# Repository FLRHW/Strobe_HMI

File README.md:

<h1 align="center">HMI board</h1>

<p align="center" width="100%">
  
</p>

***

<p align="center">
  
&nbsp; &nbsp; &nbsp; &nbsp;
  
</p>

***

# **1 kV strobe - Intro**
Since my tenage years I spend a great chunk of my spare time on hobby electronics. Back then, much of that time was to build FM transmitters, audio amplifiers and strobe lights. I was always pushing my builds as much as I could, (i.e., extracting pressurised smoke from capacitors!) as an attempt to make the flashes ever brighter. It was somewhat challenging given the limited experience and resources I had at the time, but a lot of fun nonetheless.
Life went on, priorities changed and for a long time I did not "play" with strobe lights... until recently, after I bumped into an ebay page of a large XOP-15 bulb and, well, nostalgy happened.

While defining the project scope, I had to decide if I'd use the good old Xenon bulb or move to LEDs, as these have greatly evolved and are ubiquitous nowadays, making their way to commercial strobes (https://www.martin.com/en/products/atomic-3000-led). I have decided to stick to vintage tech, as in my mind this would perhaps bring more interesting power electronics challenges, since the bulb requires a somewhat high bus voltage and can draw very high peak currents when ionised.

So that's what this repo contains: a Xenon-based strobe light, aiming to drive a XOP-15 bulb with up to 1 kV, while controlling the duration and frequency of pulses.

## Project overview
This repository contains KiCad v9 design files for the HMI board of a Xenon-based strobe light system.
The system is divided into three separate boards:
- HMI - so the user can set desired operating conditions (bus voltage, pulse width and pulse frequency)
- Main board - drives the Xenon bulb, generating the trigger pulse and actively interrupting the discharge according to the required pulse width
- Power supply - to produce an adjustable DC supply. To realise that I intend to eventually design an AC-mains powered converter, including a PFC circuit. As an interim solution, off-the-shelf boost converter modules are used: two such modules are connected in series, each providing up to 450 V output while supplied by 12 V batteries.

Working prototypes exist for both the HMI and main board. This repository covers only the HMI board. The main board is available on its own repo:
https://github.com/FLRHW/Strobe_main

The source code is kept on a separate repo:
https://github.com/FLRHW/Strobe_HMI_source

As a side project, the boost modules have been reverse engineered with the aim to modify them from non-isolated to isolated. This work is covered under the following repos:
- https://github.com/FLRHW/StepUp_module_12to450V
- https://github.com/FLRHW/Isolated_12to450V.

## Design targets
DC bus voltage: 400 V to 1000 V  
Flash rate: 0.1 Hz to 100 Hz  
Pulse duration: 20 μs to 10 ms  

Please note that extremes are not simultaneously achievable. This design relies on storing energy on a capacitor bank to then discharge it into the bulb, hence some time must be reserved for storing that energy. The pulse duration is currently limited in SW to 50 % of the period as a safeguard, but for practical use it must be a much lower percentage.

Also, the output capacitors currently in use are not large enough to reach 10 ms pulse duration - at least not at high output voltages as the bulb current seems to increase non linearly with the bus voltage.

## Intended use
This repository is intended for:
* Educational use and study of the circuit;
* Integration into hobby or research projects.

## License
The design files and documentation in this repository are released under the CERN Open Hardware Licence v2 – Permissive (CERN‑OHL‑P‑2.0). SPDX identifier: CERN-OHL-P-2.0 See the LICENSE file for the full legal text and conditions.
In short and non‑legal terms, you are free to use, modify, manufacture, and distribute hardware based on these files, provided you respect attribution requirements and the terms in the license.

## Trademarks and third‑party rights
All product names, logos, and brands eventually mentioned are the property of their respective owners and are not included or licensed here.
Any reference to third‑party marks is purely descriptive and does not imply endorsement or affiliation.

## Safety and disclaimer
* The author takes no responsibility for any injury, death or damage arising from the use, direct or indirect, of the design or otherwise any information from this repository
* You shall not build this or any prototype based on this design unless you are absolutely sure of your abilities dealing with this type of circuit
* High voltage can cause injury, death, or damage to equipment. Ensure appropriate protections and testing procedures are followed
* The design is provided as is, with no warranty of any kind
* Users are responsible for checking any patent, copyright, or regulatory constraints that may apply to their own use

***

## DIRECTORY STRUCTURE
    │
    ├─ Computations       # Misc calculations
    ├─ HTML               # HTML files for generated webpage
    ├─ Images             # Pictures and renders
    │
    ├─ kibot_resources    # External resources for KiBot
    │  ├─ colors          # Color theme for KiCad
    │  ├─ fonts           # Fonts used in the project
    │  ├─ scripts         # External scripts used with KiBot
    │  └─ templates       # Templates for KiBot generated reports
    │
    ├─ kibot_yaml         # KiBot YAML config files
    ├─ KiRI               # KiRI (PCB diff viewer) files
    │
    ├─ lib                # KiCad footprint and symbol libraries
    │  ├─ 3d_models       # Component 3D models
    │  ├─ lib_fp          # Footprint libraries
    │  └─ lib_sym         # Symbol libraries
    │
    ├─ Logos              # Logos
    │
    ├─ Manufacturing      # Assembly and fabrication documents
    │  ├─ Assembly        # Assembly documents (BoM, pos, notes)
    │  │
    │  └─ Fabrication     # Fabrication documents (ZIP, notes)
    │     ├─ Drill Tables # CSV drill tables
    │     └─ Gerbers      # Gerbers
    │
    ├─ Report             # Reports for ERC/DRC
    ├─ Schematic          # PDF of schematic
    ├─ Templates          # Title block templates
    ├─ Testing
    │  └─ Testpoints      # Testpoints tables      
    │
    └─ Variants           # Outputs for assembly variants

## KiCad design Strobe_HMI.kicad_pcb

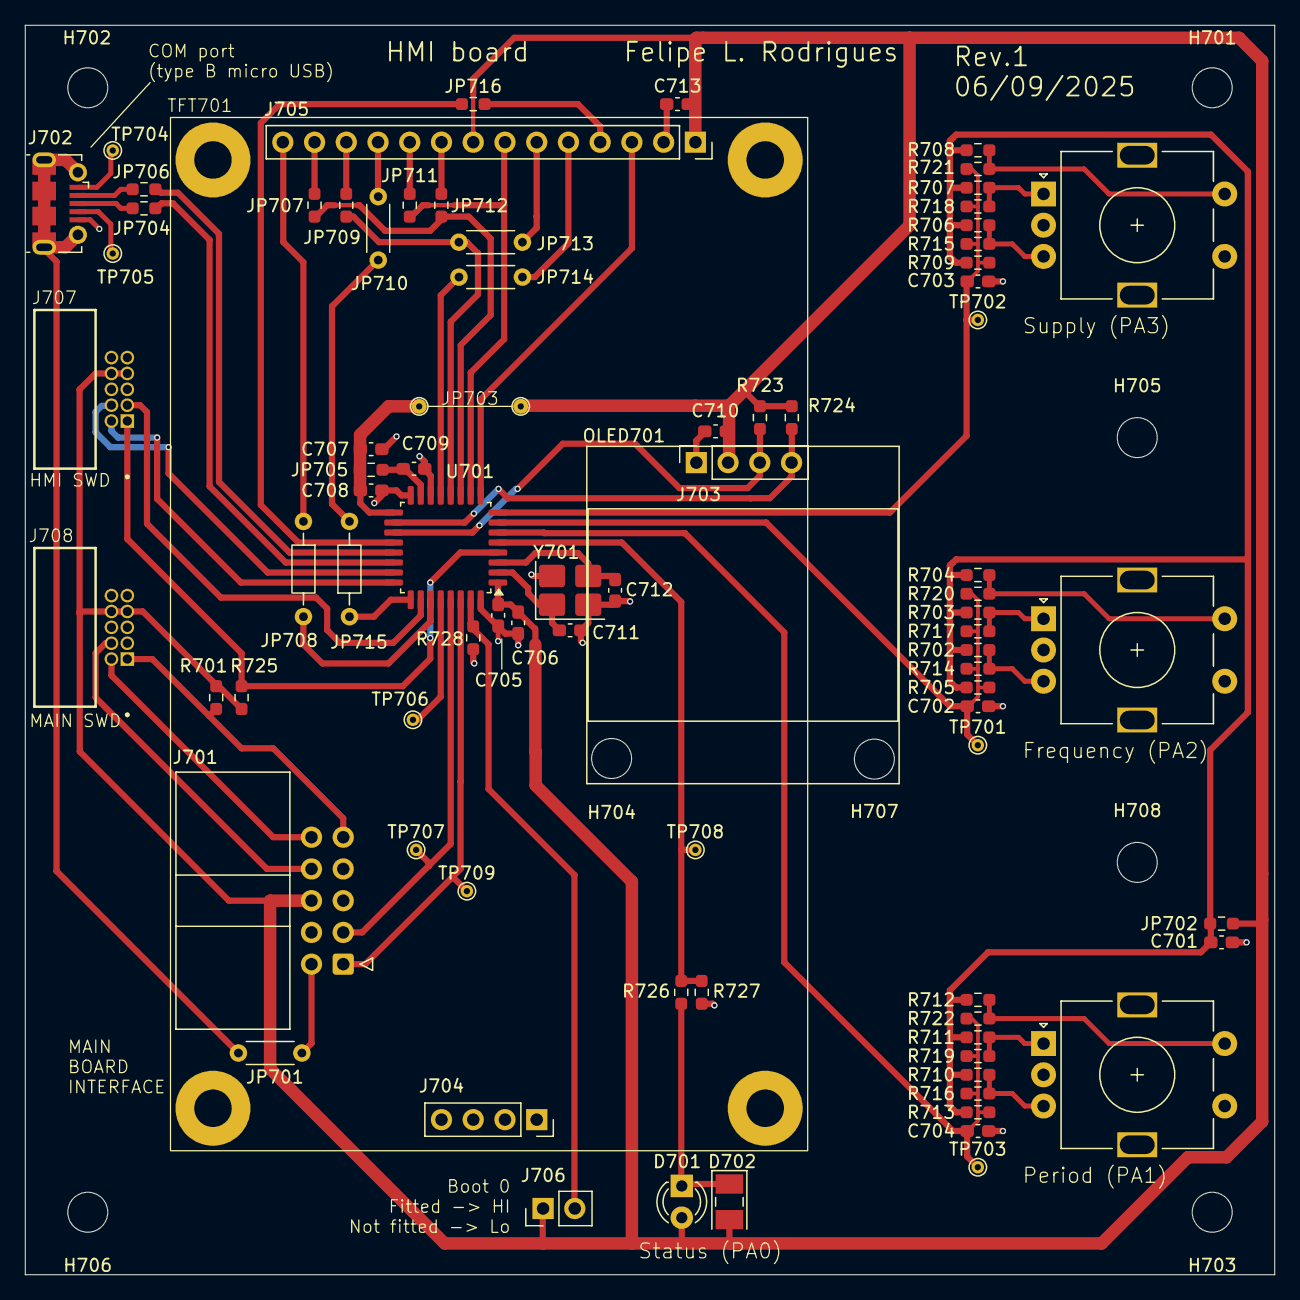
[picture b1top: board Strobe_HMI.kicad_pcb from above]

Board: 2 copper layers, 100.0 x 100.0 mm, 91 parts (0 on the bottom side), 60 nets.

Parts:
C701, C702, C703, C704, C705, C708, C709, C710, C713: 100n; C_0603_1608Metric_Pad1.08x0.95mm_HandSolder
C706, C707: 1u; C_0603_1608Metric_Pad1.08x0.95mm_HandSolder
C711, C712: 22p; C_0603_1608Metric_Pad1.08x0.95mm_HandSolder
D701: LED; LED_D3.0mm
D702: LED; LED_PLCC-2_3x2mm_KA
H701, H702, H703, H704, H705, H706, H707, H708: MountingHole; MountingHole_3.2mm_M3
J701: ZHOURI DC3; IDC-Header_2x05_P2.54mm_Horizontal
J702: 1050171001 Micro Type B; USB_Micro-B_Molex-105017-0001
J703, J704: Conn_01x04_Pin; PinSocket_1x04_P2.54mm_Vertical
J705: Conn_01x14_Pin; PinSocket_1x14_P2.54mm_Vertical
J706: Header; PinHeader_1x02_P2.54mm_Vertical
J707, J708: HX JN1.27-2x5 WZ H4.9; JN1.27-2x5 WZ H4.9
JP701, JP710, JP713, JP714: 0R; R_Axial_DIN0204_L3.6mm_D1.6mm_P5.08mm_Horizontal
JP702, JP704, JP705, JP706, JP707, JP709, JP711, JP712, JP716: 0R; R_0603_1608Metric_Pad0.98x0.95mm_HandSolder
JP703: 8.12; Jumper_mm_L8.12_D1.2_H0.5
JP708, JP715: 0R; R_Axial_DIN0204_L3.6mm_D1.6mm_P7.62mm_Horizontal
OLED701: OLED_128x64_SSD1306; OLED_SSD1306_no_pins
R701, R725, R727, R728: 10k; R_0603_1608Metric_Pad0.98x0.95mm_HandSolder
R702, R703, R704, R706, R707, R708, R710, R711, R712, R726: 1k; R_0603_1608Metric_Pad0.98x0.95mm_HandSolder
R705, R709, R713: 220k; R_0603_1608Metric_Pad0.98x0.95mm_HandSolder
R714, R715, R716: 44k; R_0603_1608Metric_Pad0.98x0.95mm_HandSolder
R717, R718, R719: 22k; R_0603_1608Metric_Pad0.98x0.95mm_HandSolder
R720, R721, R722: 11k; R_0603_1608Metric_Pad0.98x0.95mm_HandSolder
R723, R724: 4k7; R_0603_1608Metric_Pad0.98x0.95mm_HandSolder
SW701, SW702, SW703: EncSw; RotaryEncoderSwitch_Oblong
TFT701: TFT_2.8in_320x240; TFT_2.8_IN_320x240
TP701, TP702, TP703, TP704, TP705, TP706, TP707, TP708, TP709: TestPoint; TestPoint_THTPad_D1.0mm_Drill0.5mm
U701: STM32G431K8Tx; LQFP-32_7x7mm_P0.8mm
Y701: 20 MHz; Crystal_SMD_3225-4Pin_3.2x2.5mm_HandSoldering

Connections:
/Block diagram/HMI/BOOT0: J706.2, R728.1, U701.31 (PB8)
/Block diagram/HMI/DISP_CS: J705.3, U701.9 (PA4)
/Block diagram/HMI/DISP_DC: JP714.1, U701.13 (PB0)
/Block diagram/HMI/DISP_MISO: JP707.1, JP712.1, U701.11 (PA6)
/Block diagram/HMI/DISP_MOSI: JP709.1, JP713.1, U701.12 (PA7)
/Block diagram/HMI/DISP_RST: JP716.1, U701.20 (PA10)
/Block diagram/HMI/DISP_SCK: J705.7, JP711.1, U701.10 (PA5)
/Block diagram/HMI/DISP_SCL: J703.3, R723.2, U701.19 (PA9)
/Block diagram/HMI/DISP_SDA: J703.4, R724.2, U701.18 (PA8)
/Block diagram/HMI/FREQ: C702.1, R705.2, R714.2, R717.2, R720.2, TP701.1, U701.7 (PA2)
/Block diagram/HMI/LV_NRST: J701.9, J708.1, R701.2
/Block diagram/HMI/LV_RX: J701.1, TP709.1, U701.30 (PB7)
/Block diagram/HMI/LV_SWDCLK: J701.10, J708.2
/Block diagram/HMI/LV_SWDIO: J701.8, J708.4
/Block diagram/HMI/LV_TX: J701.3, TP707.1, U701.29 (PB6)
/Block diagram/HMI/NRST: J707.1, R725.2, U701.4 (PG10)
/Block diagram/HMI/PER: C704.1, R713.2, R716.2, R719.2, R722.2, TP703.1, U701.6 (PA1)
/Block diagram/HMI/SL3: C705.1, C706.1, C710.1, C713.1, D701.2 (A), D702.2 (A), J701.6, J703.2, J705.1, J705.8, J706.1, J707.7, J707.8, J708.7, J708.8, JP702.2 (B), JP703.2 (B), R701.1, R723.1, R724.1, R725.1, U701.1 (VDD)
/Block diagram/HMI/SL3_A: C709.1, JP705.2 (B), U701.15 (VDDA)
/Block diagram/HMI/SL3_J: C707.1, C708.1, JP703.1 (A), JP705.1 (A), U701.17 (VDD)
/Block diagram/HMI/ST_LED: R726.2, R727.1, TP708.1, U701.5 (PA0)
/Block diagram/HMI/SUP: C703.1, R709.2, R715.2, R718.2, R721.2, TP702.1, U701.8 (PA3)
/Block diagram/HMI/SWDCLK: J707.2, U701.24 (PA14)
/Block diagram/HMI/SWDIO: J707.4, U701.23 (PA13)
/Block diagram/HMI/SWO: J707.3, U701.26 (PB3)
/Block diagram/HMI/TCH_CS: JP710.1, JP715.2 (B)
/Block diagram/HMI/TCH_IRQ: J705.14, JP708.1 (A)
/Block diagram/HMI/USB_DM: JP706.2, U701.21 (PA11)
/Block diagram/HMI/USB_DP: JP704.2, U701.22 (PA12)
Earth: J702.6 (Shield), JP701.2
GND: C701.2, C702.2, C703.2, C704.2, C705.2, C706.2, C707.2, C708.2, C709.2, C710.2, C711.2, C712.2, C713.2, J701.5, J702.5 (GND), J703.1, J705.2, J707.5, J707.6, J708.5, J708.6, R727.2, R728.2, SW701.C, SW701.S2, SW702.C, SW702.S2, SW703.C, SW703.S2, U701.14 (VSSA), U701.16 (VSS), U701.32 (VSS), Y701.2 (G), Y701.4 (G)
unnamed: D701.1 (K), D702.1 (K), R726.1
unnamed: J701.2, JP701.1
unnamed: J702.3 (D+), JP704.1
unnamed: J702.2 (D-), JP706.1
unnamed: J702.4 (ID), TP705.1
unnamed: J702.1 (VBUS), TP704.1
unnamed: J705.4, JP716.2
unnamed: J705.5, JP714.2
unnamed: J705.6, JP713.2
unnamed: J705.9, JP712.2
unnamed: J705.10, JP711.2
unnamed: J705.11, JP710.2
unnamed: J705.12, JP709.2
unnamed: J705.13, JP707.2
unnamed: C701.1, JP702.1 (A), R702.1, R703.1, R704.1, R705.1, R706.1, R707.1, R708.1, R709.1, R710.1, R711.1, R712.1, R713.1
unnamed: JP708.2 (B), U701.27 (PB4)
unnamed: JP715.1 (A), U701.25 (PA15)
unnamed: R702.2, R714.1, SW701.B
unnamed: R703.2, R717.1, SW701.A
unnamed: R704.2, R720.1, SW701.S1
unnamed: R706.2, R715.1, SW702.B
unnamed: R707.2, R718.1, SW702.A
unnamed: R708.2, R721.1, SW702.S1
unnamed: R710.2, R716.1, SW703.B
unnamed: R711.2, R719.1, SW703.A
unnamed: R712.2, R722.1, SW703.S1
unnamed: TP706.1, U701.28 (PB5)
unnamed: C711.1, U701.2 (PF0), Y701.1
unnamed: C712.1, U701.3 (PF1), Y701.3

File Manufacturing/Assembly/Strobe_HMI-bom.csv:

Row,Quantity Per PCB,References,Value,Datasheet,Footprint,Description,Manufacturer,Manufacturer Part Number,Supplier Part Number
1,2,C711 C712,22p,~,C_0603_1608Metric_Pad1.08x0.95mm_HandSolder,Unpolarized capacitor,,,
2,8,C701 C702 C703 C704 C705 C708 C709 C713,100n,~,C_0603_1608Metric_Pad1.08x0.95mm_HandSolder,Unpolarized capacitor,,,
3,2,C706 C707,1u,~,C_0603_1608Metric_Pad1.08x0.95mm_HandSolder,Unpolarized capacitor,,,
4,1,D702,LED,~,LED_PLCC-2_3x2mm_KA,Light emitting diode,Osram,LH T6MF-GGHH-1-E3L3,
5,7,J701 J702 J704 J705 J706 J707 J708,ZHOURI DC3,~,IDC-Header_2x05_P2.54mm_Horizontal,"Generic connector, double row, 02x05, odd/even pin numbering scheme (row 1 odd numbers, row 2 even numbers), script generated (kicad-library-utils/schlib/autogen/connector/) USB Micro Type B connector Generic connector, single row, 01x04, script generated Generic connector, single row, 01x14, script generated Generic connector, single row, 01x02, script generated",,,
6,6,JP701 JP708 JP710 JP713 JP714 JP715,0R,~,R_Axial_DIN0204_L3.6mm_D1.6mm_P5.08mm_Horizontal,Jumper,Generic,Hand cut wire,
7,9,JP702 JP704 JP705 JP706 JP707 JP709 JP711 JP712 JP716,0R,~,R_0603_1608Metric_Pad0.98x0.95mm_HandSolder,Jumper,Yageo,RC0603JR-130RP,
8,1,JP703,8.12,~,Jumper_mm_L8.12_D1.2_H0.5,"Jumper, 2-pole, closed/bridged",Generic,Hand cut wire,
9,10,R702 R703 R704 R706 R707 R708 R710 R711 R712 R726,1k,~,R_0603_1608Metric_Pad0.98x0.95mm_HandSolder,Resistor,,,
10,2,R723 R724,4k7,~,R_0603_1608Metric_Pad0.98x0.95mm_HandSolder,Resistor,,,
11,4,R701 R725 R727 R728,10k,~,R_0603_1608Metric_Pad0.98x0.95mm_HandSolder,Resistor,,,
12,3,R720 R721 R722,11k,~,R_0603_1608Metric_Pad0.98x0.95mm_HandSolder,Resistor,,,
13,3,R717 R718 R719,22k,~,R_0603_1608Metric_Pad0.98x0.95mm_HandSolder,Resistor,,,
14,3,R714 R715 R716,44k,~,R_0603_1608Metric_Pad0.98x0.95mm_HandSolder,Resistor,,,
15,3,R705 R709 R713,220k,~,R_0603_1608Metric_Pad0.98x0.95mm_HandSolder,Resistor,,,
16,3,SW701 SW702 SW703,EncSw,~,RotaryEncoderSwitch_Oblong,"Rotary encoder, dual channel, incremental quadrate outputs, with switch",,,
17,1,TFT701,TFT_2.8in_320x240,,TFT_2.8_IN_320x240,,,,
18,1,U701,STM32G431K8Tx,https://www.st.com/resource/en/datasheet/stm32g431k8.pdf,LQFP-32_7x7mm_P0.8mm,"STMicroelectronics Arm Cortex-M4 MCU, 64KB flash, 32KB RAM, 170 MHz, 1.71-3.6V, 26 GPIO, LQFP32",,,
19,1,Y701,20 MHz,~,Crystal_SMD_3225-4Pin_3.2x2.5mm_HandSoldering,"Four pin crystal, GND on pins 2 and 4, small symbol",,,

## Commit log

2026-04-14 started migration
2026-04-14 Update Outputs
2026-04-14 Refactoring sch
2026-04-15 sch refactoring complete
2026-04-15 Migrated PCB file to template, switched to preliminary
2026-04-16 updated pcb template
2026-04-16 added some libraries, TFT still missing
2026-04-17 TFT 3D added
2026-04-17 Adding silk and edges to fab doc
2026-04-17 changing sheet sizes
2026-04-17 still trying to change sheet size
2026-04-18 Added code, pictures, readme, updated sch size and notes, changed to checked
2026-04-18 Preparing release
2026-04-18 added logo
2026-04-18 Updated license
2026-04-19 Ready to release
2026-04-19 Update CHANGELOG
2026-04-19 Update Outputs (release)
2026-04-26 Moved source code
2026-04-26 Changelog updated
